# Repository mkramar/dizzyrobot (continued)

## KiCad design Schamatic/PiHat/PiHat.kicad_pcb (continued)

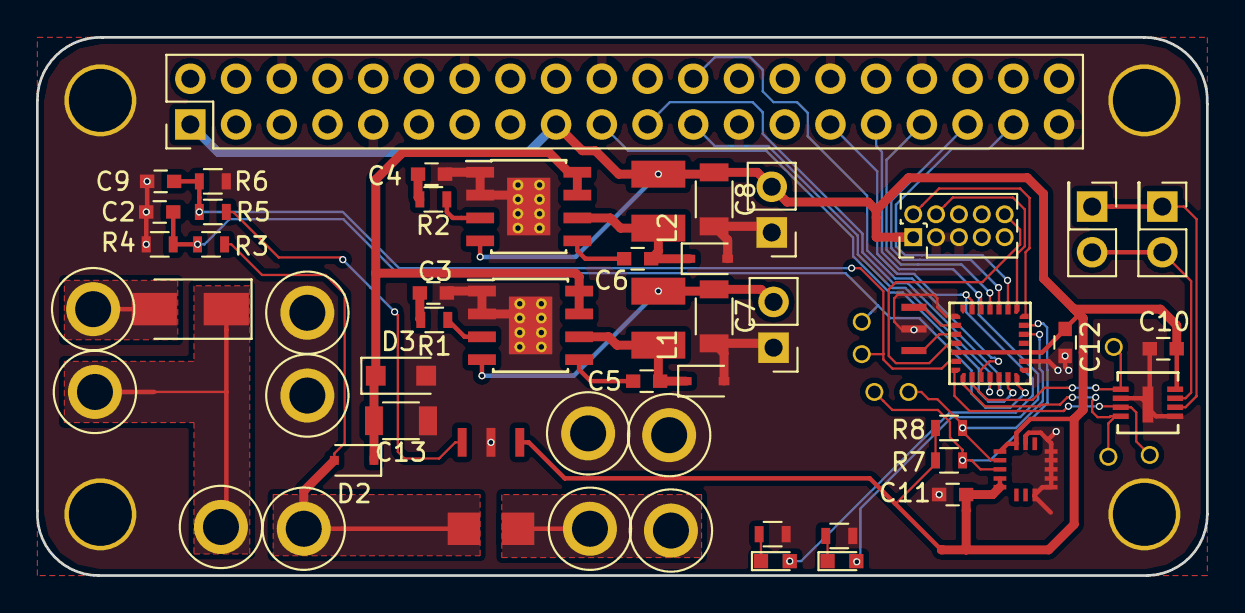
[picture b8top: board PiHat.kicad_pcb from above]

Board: 2 copper layers, 65.0 x 29.9 mm, 65 parts (0 on the bottom side), 42 nets.

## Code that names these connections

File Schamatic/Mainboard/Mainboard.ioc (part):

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Mcu.Name=STM32F031K(4-6)Ux
Mcu.Package=UFQFPN32
Mcu.UserName=STM32F031K6Ux
PA0.Mode=IN0
PA0.Signal=ADC_IN0
PA1.Mode=Hardware Flow Control (RS485)
PA1.Signal=USART1_DE
PA10.Mode=I2C
PA10.Signal=I2C1_SDA
PA13.Mode=Serial_Wire
PA13.Signal=SYS_SWDIO
PA14.Mode=Serial_Wire
PA14.Signal=SYS_SWCLK
PA2.Mode=Asynchronous
PA2.Signal=USART1_TX
PA3.Mode=Asynchronous
PA3.Signal=USART1_RX
PA4.Mode=NSS_Signal_Hard_Input
PA4.Signal=SPI1_NSS
PA5.Mode=Full_Duplex_Slave
PA5.Signal=SPI1_SCK
PA6.Mode=Full_Duplex_Slave
PA6.Signal=SPI1_MISO
PA7.Mode=Full_Duplex_Slave
PA7.Signal=SPI1_MOSI
PA9.Mode=I2C
PA9.Signal=I2C1_SCL
PB0.Mode=IN8
PB0.Signal=ADC_IN8
PB5.Signal=GPIO_Output
PB6.Signal=GPIO_Output

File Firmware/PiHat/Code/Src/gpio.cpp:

/* Includes ------------------------------------------------------------------*/
#include "gpio.h"

/** Pinout Configuration
*/
void MX_GPIO_Init(void)
{
	GPIO_InitTypeDef GPIO_InitStruct;

	  /* GPIO Ports Clock Enable */
	__HAL_RCC_GPIOF_CLK_ENABLE();
	__HAL_RCC_GPIOA_CLK_ENABLE();
	__HAL_RCC_GPIOB_CLK_ENABLE();

	  /*Configure GPIO pin Output Level */
	HAL_GPIO_WritePin(GPIOA, GPIO_PIN_15, GPIO_PIN_RESET);

	  /*Configure GPIO pin Output Level */
	HAL_GPIO_WritePin(GPIOB, GPIO_PIN_3 | GPIO_PIN_4 | GPIO_PIN_5 | GPIO_PIN_6, GPIO_PIN_RESET);

	  /*Configure GPIO pin : PA15 */
	GPIO_InitStruct.Pin = GPIO_PIN_15;
	GPIO_InitStruct.Mode = GPIO_MODE_OUTPUT_PP;
	GPIO_InitStruct.Pull = GPIO_NOPULL;
	GPIO_InitStruct.Speed = GPIO_SPEED_FREQ_LOW;
	HAL_GPIO_Init(GPIOA, &GPIO_InitStruct);

	  /*Configure GPIO pins : PB3 PB4 PB5 PB6 */
	GPIO_InitStruct.Pin = GPIO_PIN_3 | GPIO_PIN_4 | GPIO_PIN_5 | GPIO_PIN_6;
	GPIO_InitStruct.Mode = GPIO_MODE_OUTPUT_PP;
	GPIO_InitStruct.Pull = GPIO_NOPULL;
	GPIO_InitStruct.Speed = GPIO_SPEED_FREQ_LOW;
	HAL_GPIO_Init(GPIOB, &GPIO_InitStruct);
	
	//
	
  /*Configure GPIO pin : PA4 */
	GPIO_InitStruct.Pin = GPIO_PIN_4;
	GPIO_InitStruct.Mode = GPIO_MODE_IT_RISING;
	GPIO_InitStruct.Pull = GPIO_NOPULL;
	HAL_GPIO_Init(GPIOA, &GPIO_InitStruct);
	
	  /* EXTI interrupt init*/
	HAL_NVIC_SetPriority(EXTI4_15_IRQn, 0, 0);
	HAL_NVIC_EnableIRQ(EXTI4_15_IRQn);	
}

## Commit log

2017-03-25 body/part0 joint
2017-03-27 part 2 and 3
2017-03-29 part 2 printing
2017-03-29 part 1 printing
2017-03-30 part0 printing
2017-04-01 part 2 changes
2017-04-07 body and part3 printing
2017-04-08 part 3 added bearing
2017-04-09 part 1 changes
2017-04-17 starting brushless
2017-04-20 printing heap
2017-04-20 bone 1
2017-04-21 part1 printing
2017-04-25 motor pulley
2017-04-26 started part 2
2017-04-26 attempting joint with aluminium rods
2017-04-29 knee joint
2017-05-20 brushless and planetary tries
2017-05-20 started geared
2017-05-25 geared printing
2017-06-01 heap attempt
2017-06-05 started popa
2017-06-14 organized axised
2017-06-17 started enclosed
2017-06-18 print foot
2017-07-10 whatever
2017-07-12 heap
2017-07-14 heap joint holder
2017-07-26 schematic
2017-07-31 board ordered
2017-07-31 started direct
2017-08-02 large plastic parts
2017-08-02 started thigh print
2017-08-06 shin printing
2017-08-23 started body and arms
2017-09-02 first firmware for motor driver
2017-09-05 first spinning
2017-09-18 started usart
2017-09-19 usart comms
2017-09-28 new version of controller
2017-10-01 ordered controller
2017-10-03 body-heap joint
2017-10-08 foot printing
2017-10-10 waist
2017-10-13 thigh print in two parts
2017-10-14 generalized cut
2017-10-17 button press and external clock
2017-10-23 spi comm
2017-10-24 organized code into separate files
2017-10-28 TYI-motor printing, started mainboard
2017-10-28 saving
2017-10-31 constant torque turning
2017-10-31 added Release to gitignore
2017-11-03 shin print
2017-11-07 calibration saved in flash
2017-11-08 DE pin for USART
2017-11-10 usart send
2017-11-10 512 sin
2017-11-11 started layout
2017-11-11 trying to improve calibration
2017-11-12 trace done
2017-11-12 new board version ready to order
2017-11-16 dont know what it is
2017-11-22 saving before it goes too far...
2017-11-22 started thigh mold
2017-11-22 making progress on mold
2017-11-26 polishing mold framework
2017-11-27 mold framework cleanup
2017-11-28 cleanup shin printing
2017-12-03 interrupt-driver USART mold
2017-12-06 DMA USART transmit
2017-12-10 calibration looks good!
2017-12-12 new version of the board
2017-12-26 new calibration again!
2017-12-27 continue mainboard
2017-12-30 working on mainboard PCB
2017-12-31 started assigning footprints for motherboard
2018-01-01 assigned all footprints for motherboard
2018-01-02 pushbutton switch
2018-01-03 continue motherboard
2018-01-05 Adding stripped version of simplelink sdk 1_50_00_06. Ignoring XDC package in this checkin.
2018-01-05 mainboard pcb more or less complete
2018-01-06 Switched TIRTOS with freertos with gcc project
2018-01-07 motherboard minor changes
2018-01-09 Adding the uniflash project file
2018-01-10 adding freertos builds folder
2018-01-10 deleted uninstall
2018-01-10 updated gitignore to add freertos build
2018-01-10 whatever motherboard changes
2018-01-10 added some PCB components
2018-01-10 Adding few library files
2018-01-11 Updated provisioning mode to AP. Also updated the latest uniflash project file. This update is after replacing FreeRTOS 10 with 9 which solves the problem of switching to AP mode through push button.
2018-01-11 Updated LED indications. In Rev A board,
    D10 - blinking means provisioning is in progress
    D10 - Solid OFF means some error
    D10 - Solid ON means provisioning is successful
    D9 - Solid ON means device is in Station mode
    D8 - Solid ON means device is in AP mode
2018-01-12 Resetting MCU after adding profile to enable it to connect it to AP.
2018-01-12 trying to make blinking indicators
2018-01-12 both leds blink
2018-01-12 html page updated to include "Station & Client IPv4"
2018-01-12 Renamed the core project folder to "host driver".
2018-01-12 Renamed the project to "host_driver"
2018-01-15 button press and led blink
2018-01-17 RS485 hardware control
2018-01-17 more stable communication with desktop app
2018-01-17 correct byte order in test desktop app
2018-01-17 Moved all files under motherboard.
2018-01-18 Renamed out_of_box -> simplelink_handler
2018-01-18 Removed unnecessary files from metadata folder
2018-01-19 motor PCB optimization
2018-01-24 minor corrections
2018-01-27 SolidWorks 3D
2018-01-27 motherboard corrections
2018-01-30 Loopback from CC3220 -> breakout-> Rs 485 to USB communication works. Observation : in C# code in debug mode one char is received first and remaining later. the first char gets overwritten by subsequ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
2018-01-31 Tx and Rx working in both C# tool and CC3220.
2018-02-03 DMA + Interrupt working in blocking mode. Need to enable DMA in project config.
2018-02-04 Interrupt and DMA mode working after adding callback functions.
2018-02-08 removed old OpenScad 3D folder
2018-02-08 cleanup motor schematic folder
2018-02-08 logo in mask layer
2018-02-15 Both TX and TX working in DMA+Int mode. Enabled EOT interrupt and toggled RTS line based on that.
2018-02-15 Auto updated ccs files.
2018-02-15 Added tirtos package to rebuild driver library in debug mode.
2018-02-16 simple calibration
2018-02-24 updated code to add call back for torque command. This is not tested on Target.
2018-02-24 Updated web pages to send torque command
2018-02-28 PiHat
2018-03-08 starting AS548 sensor
2018-03-11 Pi hat more or less ready
2018-03-22 accumulated changes
2018-03-27 fixes to the boards
2018-04-04 corrections on body lower part
2018-04-06 removing old cc3220 mainboard
2018-04-07 starting PiHat firmware
2018-04-07 DMA receive works
2018-04-17 latest version of 3D
2018-04-21 spi communication now works
2018-04-24 current changes
2018-04-28 external motor controller
2018-05-02 USART frequencies match
2018-05-03 working on USART issues
2018-05-08 threaded serial comms
2018-05-08 MA700 sensor
2018-05-11 side-shaft calibration more or less works
2018-05-12 working on calibration
2018-05-12 calibration up and down
2018-05-14 fixed DMA so RasPI can get SPI response (again)
2018-05-15 controller-to-PiHat USART comms work in blocking mode
2018-05-15 USART comms also work with DMA
2018-05-16 approximated SIN
2018-05-17 working on stabilizing usart
2018-05-21 starting new 3D
2018-05-23 new 3D
2018-05-29 high voltage controller
2018-06-09 this was failed attempt to increase voltage
2018-06-11 high voltage controller based on AUIRS20302
2018-06-17 3D updates
2018-06-18 buttons work with STM32F031K6U6
2018-06-21 working on motherboard
2018-06-21 mainboard
2018-06-22 components allocated
2018-06-22 started mainboard PCB
2018-06-23 3d updates for new controller
2018-06-23 continue working on mainboard
2018-06-24 bigger current regulators
2018-06-25 more 3D
2018-06-28 progress
2018-06-29 5V with A1335
2018-06-30 3.3V MA700
2018-07-19 mainboard plain MOSFETS
2018-07-21 new drivers
2018-07-28 fixing schematic errors
2018-08-12 started linearization for A1335
2018-08-14 linearizaion seems to work
2018-08-18 problems with A1335 linearization, back to M700
2018-08-22 working on arm rotation
2018-09-03 3D - motor in the arm
2018-09-05 MA700 works (again). But USART doesn't :(
2018-10-10 added motors
2018-10-13 FIR filtering
2018-10-13 minor: added Mainboard.net
2018-10-14 reorganized folders
2018-10-14 re-organizing folders more
2018-10-16 started motor with external sensors
2018-11-06 Boost converter calculation
2018-11-17 starting new motor code
2018-11-17 renaming stuff
2018-11-24 started external calibration
2018-11-26 calibration kindof works
2018-11-27 calibration good
2018-11-27 timer 3 ready for temperature reading
2018-12-09 motor 8 fixes; sensor flex PCB correction.
2018-12-15 current work
2018-12-22 finished Motor 8 and Motor 6 designs
2018-12-25 saving changes
2019-01-02 gyro is working
2019-01-03 voltage and current ADC
2019-01-05 temp protection
2019-02-05 internal calibration
2019-02-15 up and down external calibration
2019-02-16 new version small motor
2019-02-25 rearrange 3D
2019-03-31 new calibration
2019-04-22 saving - calbration confusion
2019-04-22 calibration confusion
2019-04-25 calib work both up and down, but direction is still different
2019-04-25 calibration and direction seems to be fine
2019-05-02 something
2019-05-03 blocking SPI read/write. version before this one used DMA but had problems with it.
2019-05-06 working on internal calibration
2019-05-09 linearization seems to work
2019-05-23 work
2019-05-31 started driver
2019-06-01 PID controller
2019-06-06 experimenting with PID
2019-06-08 playing with new servo control method
2019-06-15 started new mainboard
2019-06-24 new mainboard
2019-07-13 body V2
2019-07-20 changes changes
2019-10-25 donno what I'm committing
2020-03-14 new model optimized for sub-assemblies and .URDF
